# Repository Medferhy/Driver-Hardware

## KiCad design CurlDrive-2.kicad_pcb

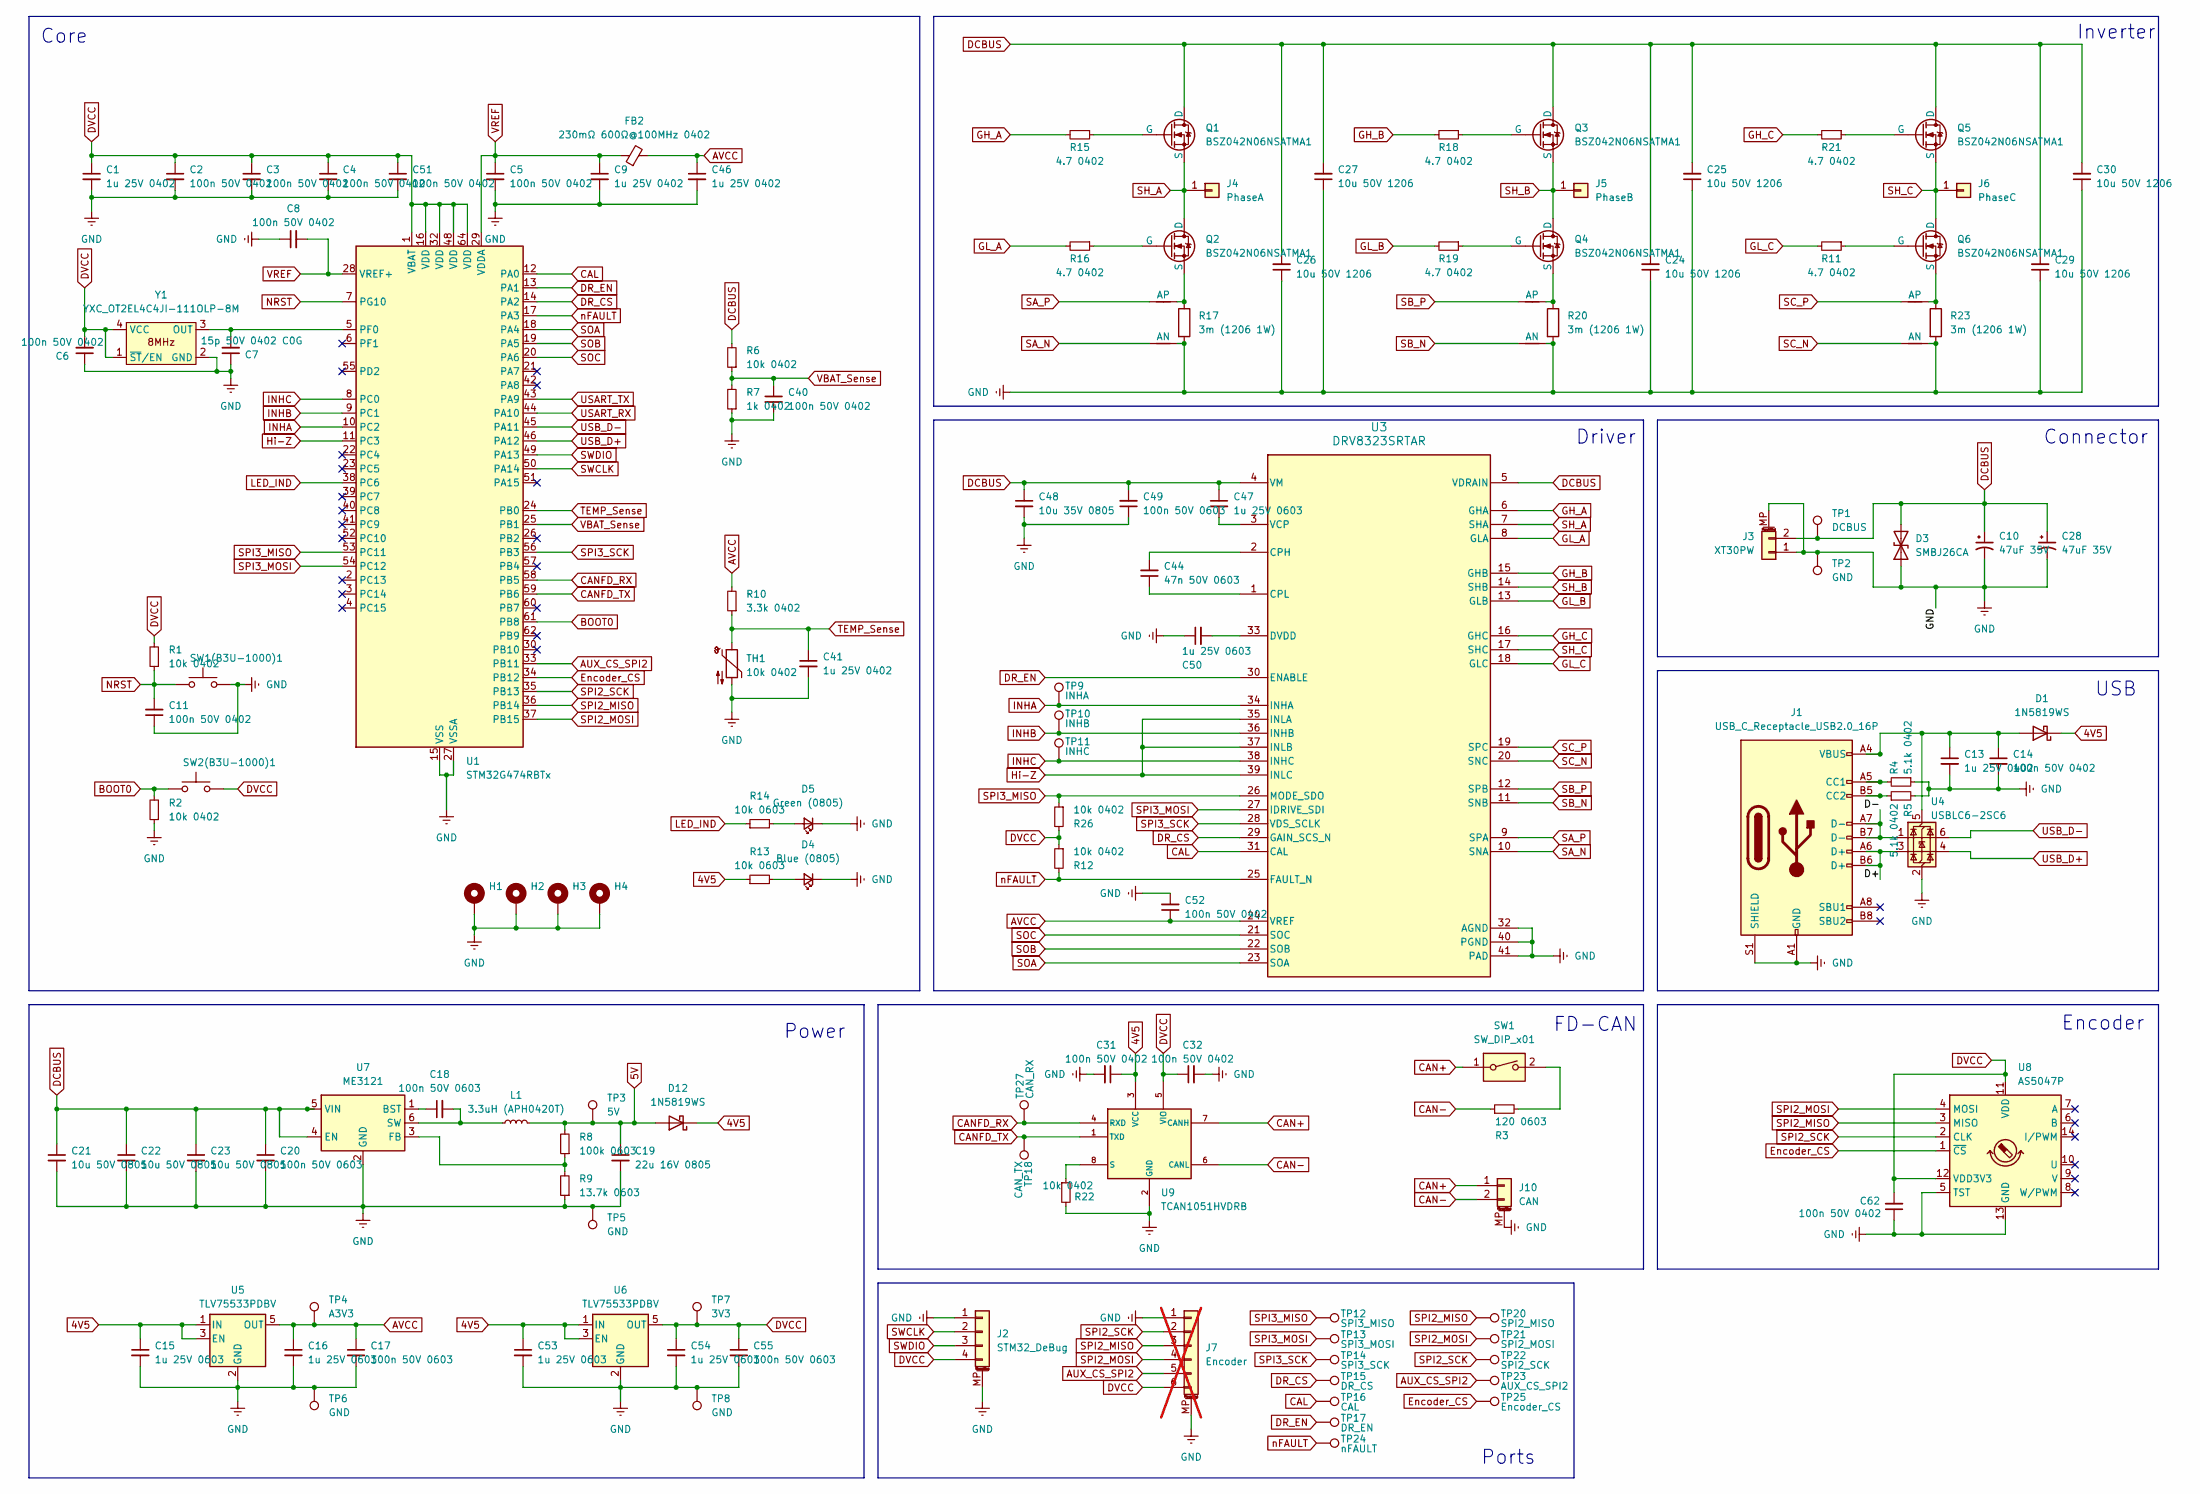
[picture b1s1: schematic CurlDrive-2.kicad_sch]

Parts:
C1, C9, C13, C41, C46: 1u 25V 0402; C_0402_1005Metric
C2, C3, C4, C5, C6, C8, C11, C14, C31, C32, C40, C51, C52, C62: 100n 50V 0402; C_0402_1005Metric
C7: 15p 50V 0402 C0G; C_0402_1005Metric
C10, C28: 47uF 35V; CP_Elec_6.3x4.9
C15, C16, C47, C50, C53, C54: 1u 25V 0603; C_0603_1608Metric
C17, C18, C20, C49, C55: 100n 50V 0603; C_0603_1608Metric
C19: 22u 16V 0805; C_0805_2012Metric
C21, C22, C23: 10u 50V 0805; C_0805_2012Metric
C24, C25, C26, C27, C29, C30: 10u 50V 1206; C_1206_3216Metric
C44: 47n 50V 0603; C_0603_1608Metric
C48: 10u 35V 0805; C_0805_2012Metric
D1, D12: 1N5819WS; D_SOD-323
D3: SMBJ26CA; D_SMB
D4: Blue (0805); LED_0805_2012Metric
D5: Green (0805); LED_0805_2012Metric
FB2: 230mΩ 600Ω@100MHz 0402; R_0402_1005Metric
H1, H2, H3, H4: MountingHole_Pad_MP; MountingHole_2.2mm_M2_DIN965_Pad
J1: USB_C_Receptacle_USB2.0_16P; USB_C_Receptacle_G-Switch_GT-USB-7010ASV
J2: STM32_DeBug; JST_SH_SM04B-SRSS-TB_1x04-1MP_P1.00mm_Horizontal
J3: XT30PW; AMASS_XT30PW-M_1x02_P2.50mm_Horizontal
J4: PhaseA; 4.5x4.5_pad
J5: PhaseB; 4.5x4.5_pad
J6: PhaseC; 4.5x4.5_pad
J7: Encoder; JST_SH_SM06B-SRSS-TB_1x06-1MP_P1.00mm_Horizontal; not fitted
J10: CAN; JST_SH_SM02B-SRSS-TB_1x02-1MP_P1.00mm_Horizontal
L1: 3.3uH (APH0420T); L_APV_APH0420
NT1, NT3, NT5: AP; NetTie-2
NT2, NT4, NT6: AN; NetTie-2
Q1, Q2, Q3, Q4, Q5, Q6: BSZ042N06NSATMA1; PG-TSDSON-8
R1, R2, R6, R12, R22, R26: 10k 0402; R_0402_1005Metric
R3: 120 0603; R_0603_1608Metric
R4, R5: 5.1k 0402; R_0402_1005Metric
R7: 1k 0402; R_0402_1005Metric
R8: 100k 0603; R_0603_1608Metric
R9: 13.7k 0603; R_0603_1608Metric
R10: 3.3k 0402; R_0402_1005Metric
R11, R15, R16, R18, R19, R21: 4.7 0402; R_0402_1005Metric
R13, R14: 10k 0603; R_0603_1608Metric
R17, R20, R23: 3m (1206 1W); R_1206_3216Metric
SW1: SW_DIP_x01; SW_SPST_DSHP-01-TJ-GER
SW1(B3U-1000)1, SW2(B3U-1000)1: SW_Push; SW_SPST_B3U-1000P
TH1: 10k 0402; R_0402_1005Metric
TP1: DCBUS; TestPoint_Pad_D0.4mm
TP2, TP5, TP6, TP8: GND; TestPoint_Pad_D0.4mm
TP3: 5V; TestPoint_Pad_D0.4mm
TP4: A3V3; TestPoint_Pad_D0.4mm
TP7: 3V3; TestPoint_Pad_D0.4mm
TP9: INHA; TestPoint_Pad_D0.4mm
TP10: INHB; TestPoint_Pad_D0.4mm
TP11: INHC; TestPoint_Pad_D0.4mm
TP12: SPI3_MISO; TestPoint_Pad_D0.4mm
TP13: SPI3_MOSI; TestPoint_Pad_D0.4mm
TP14: SPI3_SCK; TestPoint_Pad_D0.4mm
TP15: DR_CS; TestPoint_Pad_D0.4mm
TP16: CAL; TestPoint_Pad_D0.4mm
TP17: DR_EN; TestPoint_Pad_D0.4mm
TP18: CAN_TX; TestPoint_Pad_D0.4mm
TP20: SPI2_MISO; TestPoint_Pad_D0.4mm
TP21: SPI2_MOSI; TestPoint_Pad_D0.4mm
TP22: SPI2_SCK; TestPoint_Pad_D0.4mm
TP23: AUX_CS_SPI2; TestPoint_Pad_D0.4mm
TP24: nFAULT; TestPoint_Pad_D0.4mm
TP25: Encoder_CS; TestPoint_Pad_D0.4mm
TP27: CAN_RX; TestPoint_Pad_D0.4mm
U1: STM32G474RBTx; LQFP-64_10x10mm_P0.5mm
U3: DRV8323SRTAR; DRV8323
U4: USBLC6-2SC6; SOT-23-6
U5, U6: TLV75533PDBV; SOT-23-5
U7: ME3121; SOT-23-6
U8: AS5047P; TSSOP-14_4.4x5mm_P0.65mm
U9: TCAN1051HVDRB; TCAN1051VDRB
Y1: YXC_OT2EL4C4JI-111OLP-8M; Crystal_SMD_3225-4Pin_3.2x2.5mm

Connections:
4V5: C15.1, C31.1, C53.1, D1.1 (K), D12.1 (K), R13.1, U5.1 (IN), U5.3 (EN), U6.1 (IN), U6.3 (EN), U9.3 (VCC)
5V: C19.1, D12.2 (A), L1.2, R8.2, TP3.1
/D+: J1.A6 (D+), J1.B6 (D+), U4.3 (I/O2)
/D-: J1.A7 (D-), J1.B7 (D-), U4.1 (I/O1)
AUX_CS_SPI2: J7.5, TP23.1, U1.33 (PB11)
AVCC: C16.1, C17.1, C46.1, C52.1, FB2.2, R10.2, TP4.1, U3.24 (VREF), U5.5 (OUT)
BOOT0: R2.2, SW2(B3U-1000)1.1, U1.61 (PB8)
CAL: TP16.1, U1.12 (PA0), U3.31 (CAL)
CAN+: J10.1, SW1.1, U9.7 (CANH)
CAN-: J10.2, R3.1, U9.6 (CANL)
CANFD_RX: TP27.1, U1.58 (PB5), U9.4 (RXD)
CANFD_TX: TP18.1, U1.59 (PB6), U9.1 (TXD)
DCBUS: C10.1, C20.1, C21.1, C22.1, C23.1, C24.2, C25.2, C26.2, C27.2, C28.1, C29.2, C30.2, C47.1, C48.1, C49.2, D3.2 (A2), J3.2, Q1.1 (D), Q3.1 (D), Q5.1 (D), R6.2, TP1.1, U3.4 (VM), U3.5 (VDRAIN), U7.4 (EN), U7.5 (VIN)
DR_CS: TP15.1, U1.14 (PA2), U3.29 (GAIN_SCS_N)
DR_EN: TP17.1, U1.13 (PA1), U3.30 (ENABLE)
DVCC: C1.1, C2.1, C3.1, C4.1, C6.2, C32.1, C51.1, C54.1, C55.1, C62.2, J2.4, J7.6, R1.2, R12.1, R26.2, SW2(B3U-1000)1.2, TP7.1, U1.1 (VBAT), U1.16 (VDD), U1.32 (VDD), U1.48 (VDD), U1.64 (VDD), U6.5 (OUT), U8.11 (VDD), U8.12 (VDD3V3), U9.5 (VIO), Y1.1 (~ST/EN), Y1.4 (VCC)
Encoder_CS: TP25.1, U1.34 (PB12), U8.1 (~CS)
GH_A: R15.2, U3.6 (GHA)
GH_B: R18.2, U3.15 (GHB)
GH_C: R21.2, U3.16 (GHC)
GL_A: R16.2, U3.8 (GLA)
GL_B: R19.2, U3.13 (GLB)
GL_C: R11.2, U3.18 (GLC)
GND: C1.2, C2.2, C3.2, C4.2, C5.2, C6.1, C7.1, C8.1, C9.2, C10.2, C11.1, C13.2, C14.2, C15.2, C16.2, C17.2, C19.2, C20.2, C21.2, C22.2, C23.2, C24.1, C25.1, C26.1, C27.1, C28.2, C29.1, C30.1, C31.2, C32.2, C40.2, C41.2, C46.2, C48.2, C49.1, C50.1, C51.2, C52.2, C53.2, C54.2, C55.2, C62.1, D3.1 (A1), D4.1 (K), D5.1 (K), H1.MP, H2.MP, H3.MP, H4.MP, J1.A1 (GND), J1.A12 (GND), J1.B1 (GND), J1.B12 (GND), J1.S1 (SHIELD), J2.1, J2.MP (MountPin), J3.1, J3.MP (MountPin), J7.1, J7.MP (MountPin), J10.MP (MountPin), NT2.2, NT4.2, NT6.2, R2.1, R4.1, R5.2, R7.1, R9.1, R17.2, R20.2, R22.2, R23.2, SW1(B3U-1000)1.2, TH1.2, TP2.1, TP5.1, TP6.1, TP8.1, U1.15 (VSS), U1.27 (VSSA), U1.31 (VSS), U1.47 (VSS), U1.63 (VSS), U3.32 (AGND), U3.40 (PGND), U3.41 (PAD), U4.2 (GND), U5.2 (GND), U6.2 (GND), U7.2 (GND), U8.5 (TST), U8.13 (GND), U9.2 (GND), Y1.2 (GND)
Hi-Z: U1.11 (PC3), U3.35 (INLA), U3.37 (INLB), U3.39 (INLC)
INHA: TP9.1, U1.10 (PC2), U3.34 (INHA)
INHB: TP10.1, U1.9 (PC1), U3.36 (INHB)
INHC: TP11.1, U1.8 (PC0), U3.38 (INHC)
LED_IND: R14.1, U1.38 (PC6)
NRST: C11.2, R1.1, SW1(B3U-1000)1.1, U1.7 (PG10)
unnamed: C13.1, C14.1, D1.2 (A), J1.A4 (VBUS), J1.A9 (VBUS), J1.B4 (VBUS), J1.B9 (VBUS), U4.5 (VBUS)
unnamed: D4.2 (A), R13.2
unnamed: D5.2 (A), R14.2
unnamed: J1.A5 (CC1), R4.2
unnamed: J1.B5 (CC2), R5.1
unnamed: Q1.2 (G), R15.1
unnamed: Q2.2 (G), R16.1
unnamed: NT1.2, Q2.3 (S), R17.1
unnamed: Q3.2 (G), R18.1
unnamed: Q4.2 (G), R19.1
unnamed: NT3.2, Q4.3 (S), R20.1
unnamed: Q5.2 (G), R21.1
unnamed: Q6.2 (G), R11.1
unnamed: NT5.2, Q6.3 (S), R23.1
unnamed: R3.2, SW1.2
unnamed: C7.2, U1.5 (PF0), Y1.3 (OUT)
unnamed: C44.2, U3.2 (CPH)
unnamed: C44.1, U3.1 (CPL)
unnamed: C50.2, U3.33 (DVDD)
unnamed: C47.2, U3.3 (VCP)
unnamed: C18.1, U7.1 (BST)
unnamed: R8.1, R9.2, U7.3 (FB)
unnamed: C18.2, L1.1, U7.6 (SW)
unnamed: R22.1, U9.8 (S)
SA_N: NT2.1, U3.10 (SNA)
SA_P: NT1.1, U3.9 (SPA)
SB_N: NT4.1, U3.11 (SNB)
SB_P: NT3.1, U3.12 (SPB)
SC_N: NT6.1, U3.20 (SNC)
SC_P: NT5.1, U3.19 (SPC)
SH_A: J4.1, Q1.3 (S), Q2.1 (D), U3.7 (SHA)
SH_B: J5.1, Q3.3 (S), Q4.1 (D), U3.14 (SHB)
SH_C: J6.1, Q5.3 (S), Q6.1 (D), U3.17 (SHC)
SOA: U1.18 (PA4), U3.23 (SOA)
SOB: U1.19 (PA5), U3.22 (SOB)
SOC: U1.20 (PA6), U3.21 (SOC)
SPI2_MISO: J7.3, TP20.1, U1.36 (PB14), U8.3 (MISO)
SPI2_MOSI: J7.4, TP21.1, U1.37 (PB15), U8.4 (MOSI)
SPI2_SCK: J7.2, TP22.1, U1.35 (PB13), U8.2 (CLK)
SPI3_MISO: R26.1, TP12.1, U1.53 (PC11), U3.26 (MODE_SDO)
SPI3_MOSI: TP13.1, U1.54 (PC12), U3.27 (IDRIVE_SDI)
SPI3_SCK: TP14.1, U1.56 (PB3), U3.28 (VDS_SCLK)
SWCLK: J2.2, U1.50 (PA14)
SWDIO: J2.3, U1.49 (PA13)
TEMP_Sense: C41.1, R10.1, TH1.1, U1.24 (PB0)
USART_RX: U1.44 (PA10)
USART_TX: U1.43 (PA9)
USB_D+: U1.46 (PA12), U4.4 (I/O2)
USB_D-: U1.45 (PA11), U4.6 (I/O1)
VBAT_Sense: C40.1, R6.1, R7.2, U1.25 (PB1)
VREF: C5.1, C8.2, C9.1, FB2.1, U1.28 (VREF+), U1.29 (VDDA)
nFAULT: R12.2, TP24.1, U1.17 (PA3), U3.25 (FAULT_N)

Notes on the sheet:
Power
Core
Driver
Ports
Encoder
USB
Connector
Inverter
FD-CAN

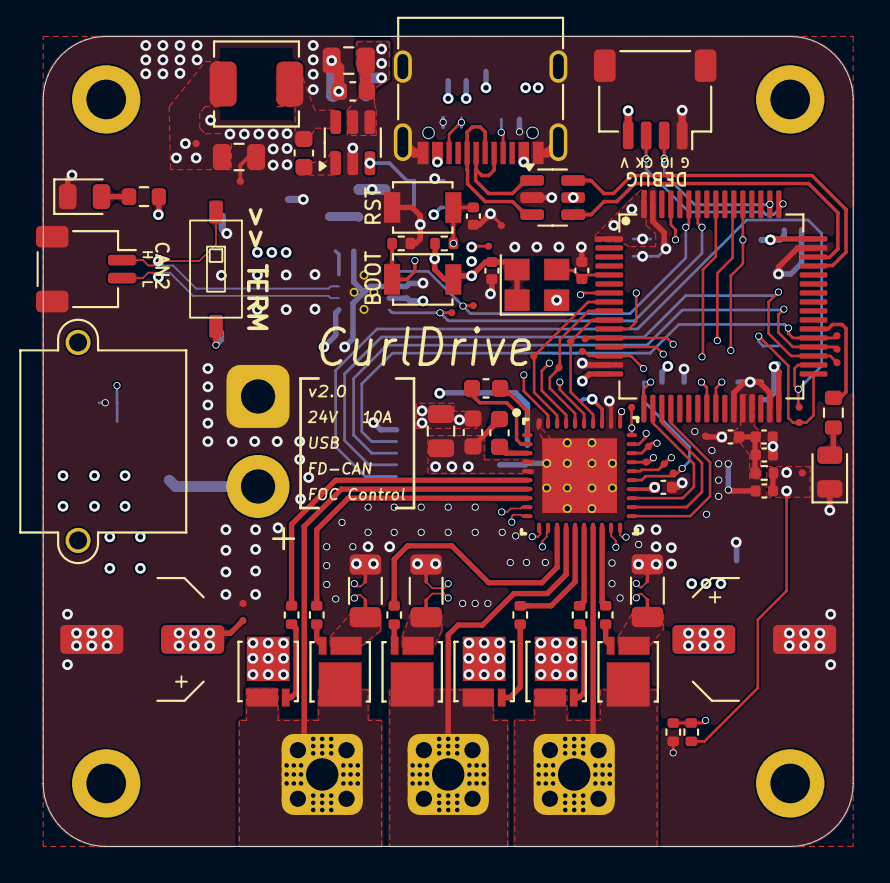
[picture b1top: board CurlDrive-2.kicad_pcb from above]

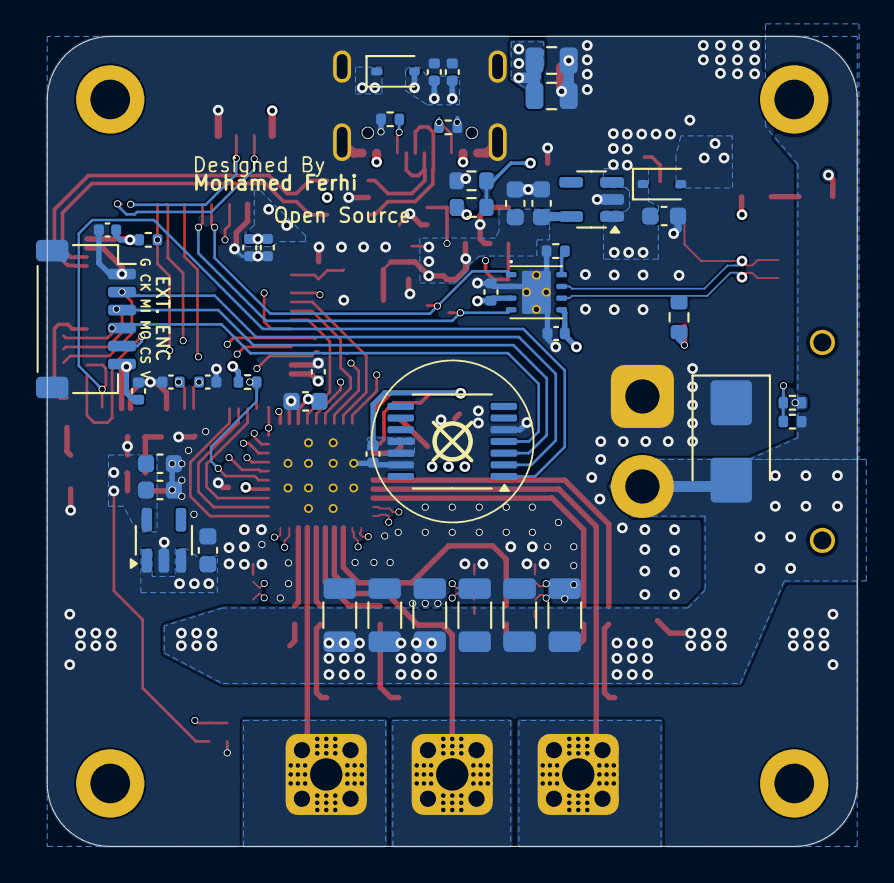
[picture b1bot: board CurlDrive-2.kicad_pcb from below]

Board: 6 copper layers, 45.0 x 45.0 mm, 138 parts (45 on the bottom side), 80 nets.
